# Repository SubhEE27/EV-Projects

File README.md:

# ⚡ Electric Vehicle Projects 🚗

This repository showcases my work in **Electric Vehicle (EV) system design**, focusing on **MATLAB/Simulink simulations**, **custom PCB development**, and a **3D CAD model** of an e-rickshaw. These projects combine theoretical modeling with hands-on engineering to develop subsystems of electric mobility solutions.

---

## 🛠️ Technologies & Tools Used

- **Simulation:** MATLAB/Simulink
- **PCB Design:** Autodesk Eagle, Fusion 360 Electronics
- **3D CAD Modeling:** Autodesk Fusion 360
- **Microcontroller Integration:** Arduino, ESP32

---

## 📁 Repository Structure

/MATLAB_Simulations/
├── BLDC_Motor_Control/
├── Power_Management_System/
└── Regenerative_Braking_Model/

/PCB_Designs/
├── Motor_Controller_PCB/
└── Battery_Management_PCB/

/3D_CAD_Model/
└── E_Rickshaw_Model.f3d

---

## ⚙️ Project Highlights

### 🔷 MATLAB/Simulink Simulations

1. **BLDC Motor Control**
   - Implemented 6-step commutation with inverter, PI control loop, and DC-link filtering
   - Simulated torque and speed control for efficient motor drive

---

### 🟢 PCB Development

1. **Motor Controller PCB**
   - Designed multi-layer PCB with gate drivers, MOSFETs, and microcontroller interface
   - Integrated feedback sensors and protection circuitry
     
---

### 🟠 3D CAD: E-Rickshaw Model

- Created a **full 3D assembly model** of an e-rickshaw using **Fusion 360**
- Includes chassis, battery housing, motor mount, and cabin
- Useful for mechanical layout planning and integration with electronics

---

## 🚀 Getting Started

### Requirements
- MATLAB R2021b or later with Simscape and Simulink
- Autodesk Eagle or Fusion 360 for PCB and CAD files
- LTspice (optional for analog circuit validation)

### How to Use
- Open `.slx` files in MATLAB/Simulink to simulate system behavior
- Open `.brd` or `.f3d` files in Eagle or Fusion 360 for design viewing or editing
- Each folder contains documentation, schematics, and simulation data

---

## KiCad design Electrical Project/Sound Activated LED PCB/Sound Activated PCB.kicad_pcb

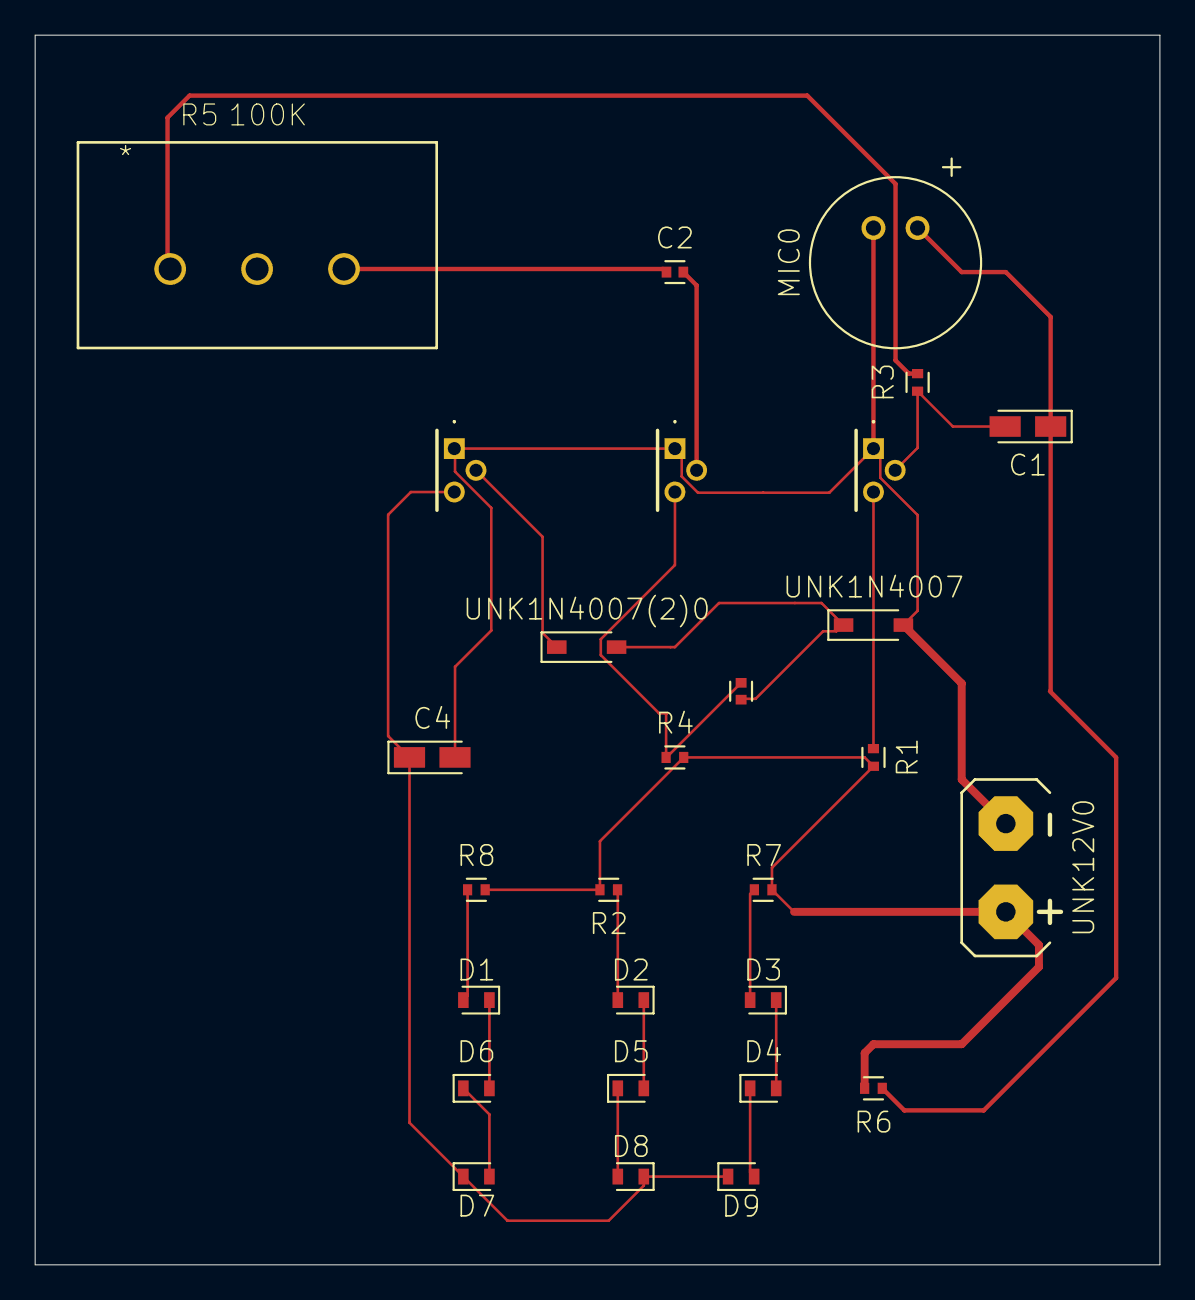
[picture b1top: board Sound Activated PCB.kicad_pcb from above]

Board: 2 copper layers, 64.8 x 70.8 mm, 28 parts (0 on the bottom side), 21 nets.

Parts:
C1: 100nF; CAPMP3216X180N_16290819
C2: 100nF; CAPC1005X60_16290819
C3: 0.1u; CAPC1005X60_16290819
C4: 1u; CAPMP3216X180N_16290819
D1, D2, D3, D4, D5, D6, D7, D8, D9: CHIP-ROUND-R_0603; LEDC1608X65N_RND-R_22900745
MIC0: CMA-4544PF-W; CMA-4544PF-W_24934241
Q1, Q2, Q3: 2N4401-T; 2N4401T
R1: 220K; RESC1005X40_16378527
R2, R7, R8: 470; RESC1005X40_16378527
R3: 660K; RESC1005X40_16378527
R4: 1.2K; RESC1005X40_16378527
R5: 100K; POT_1623757-2_14809352
R6: 10K; RESC1005X40_16378527
UNK1N4007, UNK1N4007(2)0: DIODE_1N4148W-7-F_SOD123G; SOD3715X135_16378169
UNK12V0: BATTERYGENERIC; BATTERY-GENERIC_30890021

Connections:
unnamed: C1.1, MIC0.1, R6.1
unnamed: D1.A, R8.1
unnamed: Q1.3, R1.1
unnamed: C4.2, MIC0.2, Q1.1, Q2.1, Q3.1, UNK1N4007.2, UNK12V0.-
unnamed: C1.2, Q1.2, R3.1
unnamed: R3.2, R5.1
unnamed: C2.1, R5.3
unnamed: C2.2, Q2.2
unnamed: C3.1, Q2.3, R4.1
unnamed: R1.2, R2.2, R4.2, R6.2, R7.2, R8.2, UNK12V0.+
unnamed: D2.A, R2.1
unnamed: D3.A, R7.1
unnamed: D1.C, D6.A
unnamed: D2.C, D5.A
unnamed: D3.C, D4.A
unnamed: D6.C, D7.A
unnamed: D5.C, D8.A
unnamed: D4.C, D9.A
unnamed: C4.1, D7.C, D8.C, D9.C, Q3.3
unnamed: C3.2, UNK1N4007.1, UNK1N4007(2)0.2
unnamed: Q3.2, UNK1N4007(2)0.1

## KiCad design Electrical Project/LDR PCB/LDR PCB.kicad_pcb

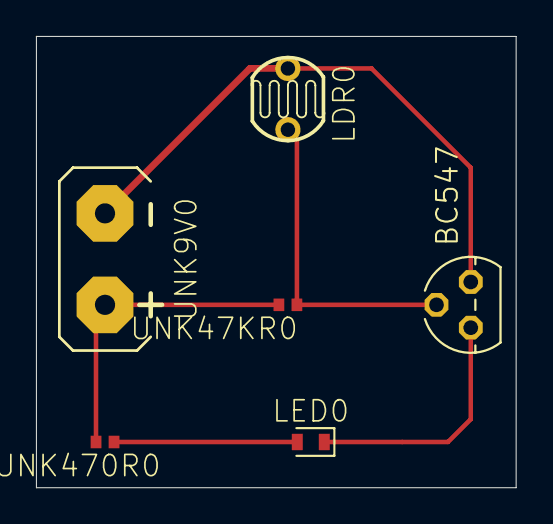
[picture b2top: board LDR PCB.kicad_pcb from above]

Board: 2 copper layers, 26.7 x 25.1 mm, 6 parts (0 on the bottom side), 5 nets.

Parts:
BC547: BC547; TO92_402
LDR0: PHOTOCELL_GL5528; GL5528_30890021
LED0: CHIP-ROUND-R_0603; LEDC1608X65N_RND-R_22900745
UNK9V0: BATTERY-9VGENERIC; BATTERY-GENERIC_30890021
UNK47KR0: 47K; R0402_334
UNK470R0: 470; R0402_334

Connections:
unnamed: BC547.1, LDR0.2, UNK9V0.-
unnamed: BC547.2, LDR0.1, UNK47KR0.1
unnamed: BC547.3, LED0.C
unnamed: LED0.A, UNK470R0.1
unnamed: UNK9V0.+, UNK47KR0.2, UNK470R0.2

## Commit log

2025-07-17 README.md
2025-07-17 gfb.txt
2025-07-17 gvg.txt
2025-07-17 gfg.txt
2025-07-17 fg.txt
2025-07-17 hgh.txt
